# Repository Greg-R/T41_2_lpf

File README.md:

The documentation for this module is located here:

<https://kf5n.com/t41-2/t41-2_lpf/>

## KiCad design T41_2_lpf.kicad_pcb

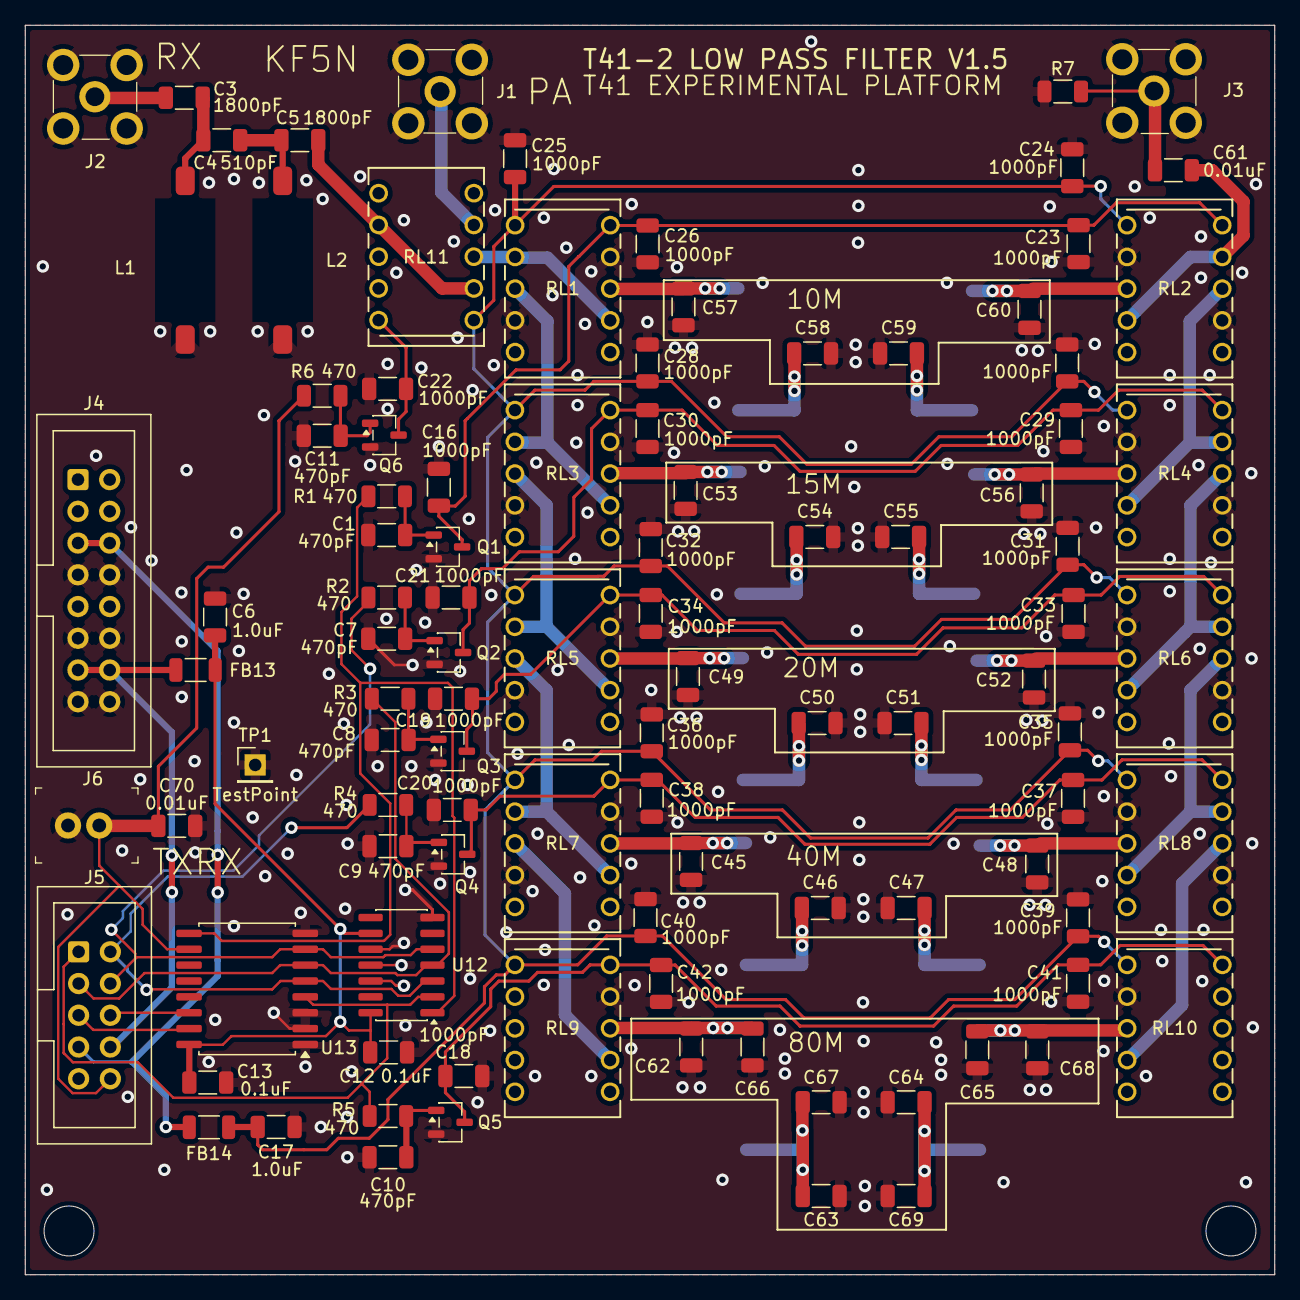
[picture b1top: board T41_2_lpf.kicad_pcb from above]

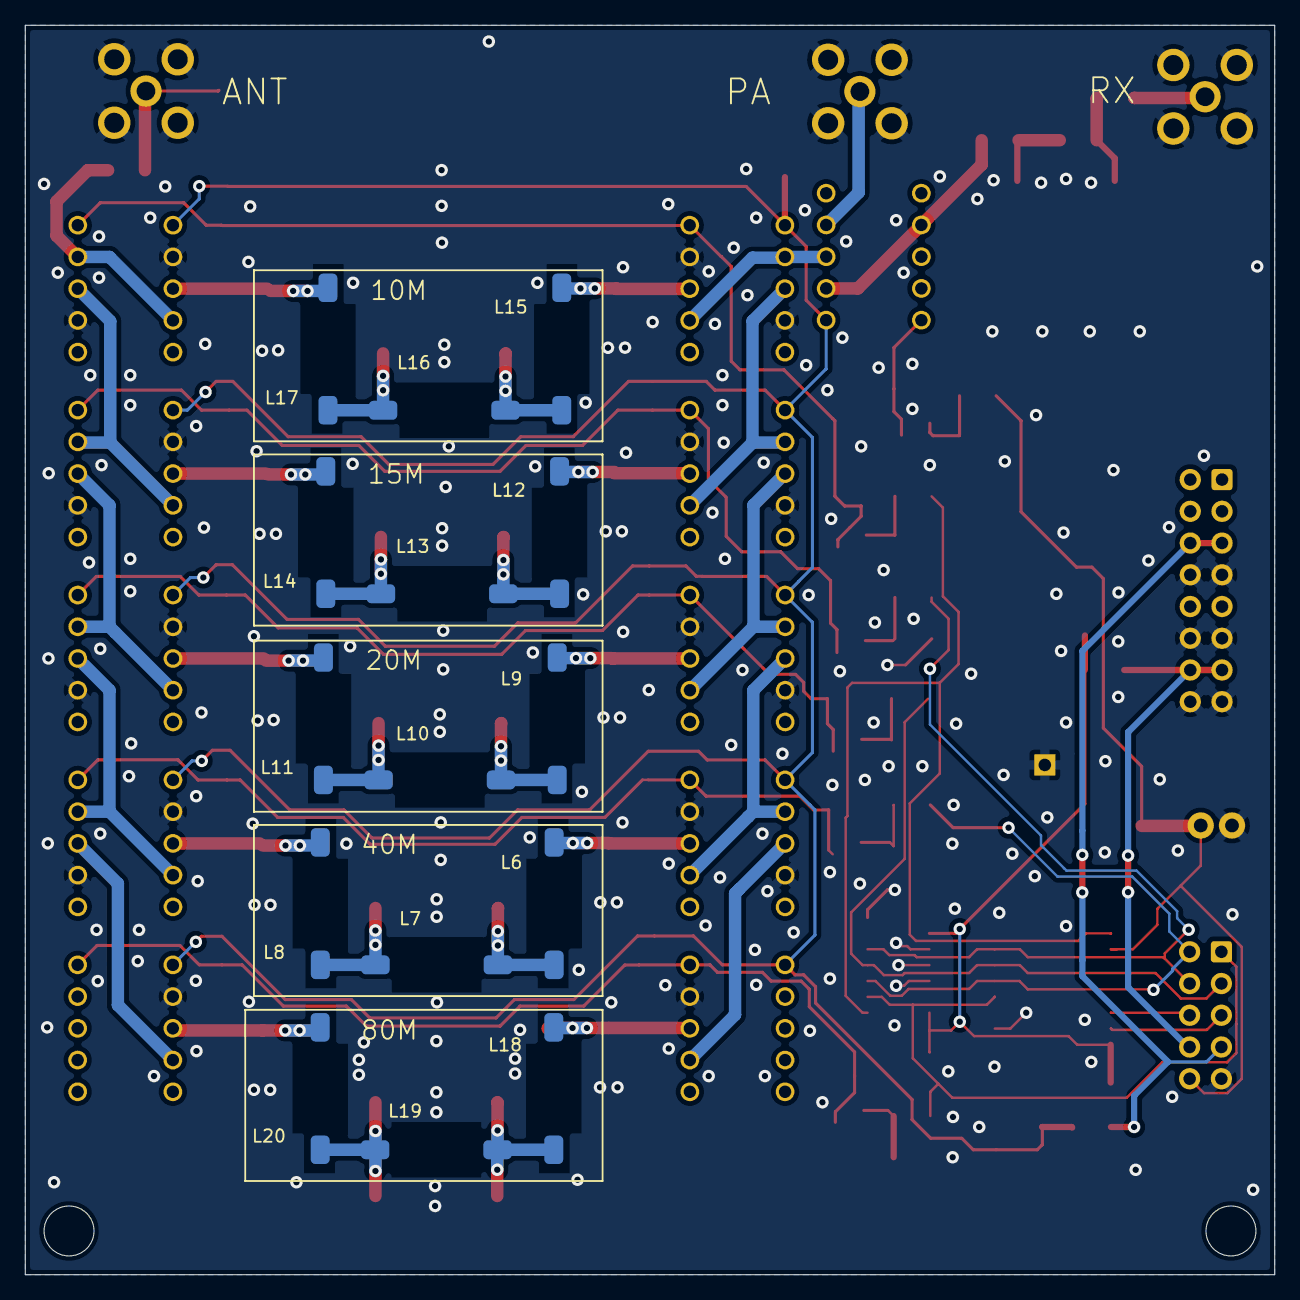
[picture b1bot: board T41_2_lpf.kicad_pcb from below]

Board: 2 copper layers, 100.0 x 100.0 mm, 117 parts (15 on the bottom side), 61 nets.

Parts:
C1, C7, C8, C9, C10, C11: 470pF; C_1206_3216Metric
C3, C5: 1800pF; C_1206_3216Metric
C4, C45, C48: 510pF; C_1206_3216Metric
C6, C17: 1.0uF; C_1206_3216Metric
C12, C13: 0.1uF; C_1206_3216Metric
C16, C18, C19, C20, C21, C22, C23, C24, C25, C26, C27, C28, C29, C30, C31, C32, C33, C34, C35, C36, C37, C38, C39, C40, C41, C42, C64, C65, C66, C67: 1000pF; C_1206_3216Metric
C46, C47: 1100pF; C_1206_3216Metric
C49, C52, C58, C59: 300pF; C_1206_3216Metric
C50, C51: 560pF; C_1206_3216Metric
C53, C56: 200pF; C_1206_3216Metric
C54, C55: 360pF; C_1206_3216Metric
C57, C60: 150pF; C_1206_3216Metric
C61, C70: 0.01uF; C_1206_3216Metric
C62, C68: 430pF; C_1206_3216Metric
C63, C69: 1500pF; C_1206_3216Metric
FB13, FB14: 28F0121-0SR-10; L_1206_3216Metric
J1, J2, J3: 5-1814832-1; RF_SMA_Vertical_5-1814832-1
J4: Conn_02x08_Odd_Even; IDC-Header_2x08_P2.54mm_Vertical
J5: Conn_02x05_Odd_Even; IDC-Header_2x05_P2.54mm_Vertical
J6: B2B-XH-A_LF__SN_; PinHeader_1x2_P2.5mm_Drill1.1mm
L1, L2: L; Toroid_SMD_T68
L6, L7, L8, L9, L10, L11, L12, L13, L14, L15, L16, L17, L18, L19, L20: L; Toroid_SMD_Thin
Q1, Q2, Q3, Q4, Q5, Q6: Q_NMOS_GSD; SOT-23-3
R1, R2, R3, R4, R5, R6: 470; R_1206_3216Metric
R7: 100k; R_1206_3216Metric
RL1, RL2, RL3, RL4, RL5, RL6, RL7, RL8, RL9, RL10, RL11: RELAY_TQ2_PAN
TP1: TestPoint; PinHeader_1x01_P2.54mm_Vertical
U12: 4002; SOIC-14_3.9x8.7mm_P1.27mm
U13: TCA9534; SOIC-16W_7.5x10.3mm_P1.27mm

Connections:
/3_3V_FIL: C6.1, C12.1, C13.1, FB13.2, U12.9, U12.14 (VDD), U13.16 (VDD)
/3_3V_IN: FB13.1, J4.13, J4.14, J5.8
/10M_ON: R1.1, U12.1, U13.9 (P4)
/12V_IN: FB14.1, J4.5, J4.6, J5.7
/12V_RELAY: C17.1, C24.2, C25.2, C27.2, C28.2, C31.2, C32.2, C35.2, C36.2, C39.2, C40.2, FB14.2, RL1.1, RL2.1, RL3.1, RL4.1, RL5.1, RL6.1, RL7.1, RL8.1, RL9.1, RL10.1, RL11.1
/15M_ON: J5.4, R2.1, U12.5, U13.7 (P3)
/20M_ON: J5.3, R3.1, U12.4, U13.6 (P2)
/40M_ON: J5.2, R4.1, U12.3, U13.5 (P1)
/80M_ON: J5.1, R5.1, U12.2, U13.4 (P0)
/Filter1/Input: C45.2, L6.1, RL7.8
/Filter1/Output: C48.2, L8.2, RL8.3
/Filter2/Input: C49.2, L9.1, RL5.8
/Filter2/Output: C52.2, L11.2, RL6.3
/Filter3/Input: C53.2, L12.1, RL3.8
/Filter3/Output: C56.2, L14.2, RL4.3
/Filter4/Input: C57.2, L15.1, RL1.8
/Filter4/Output: C60.2, L17.2, RL2.3
/Filter5/Input: C62.2, C66.2, L18.1, RL9.8
/Filter5/Output: C65.2, C68.2, L20.2, RL10.3
/SCL: J5.6, U13.14 (SCL)
/SDA: J5.5, U13.15 (SDA)
/TXRX: C70.1, J5.10, J6.2, R6.1, U13.10 (P5)
GND: C1.2, C6.2, C7.2, C8.2, C9.2, C10.2, C11.2, C12.2, C13.2, C16.2, C17.2, C18.2, C19.2, C20.2, C21.2, C22.2, C23.2, C24.1, C25.1, C26.2, C27.1, C28.1, C29.2, C30.2, C31.1, C32.1, C33.2, C34.2, C35.1, C36.1, C37.2, C38.2, C39.1, C40.1, C41.2, C42.2, C45.1, C46.1, C47.1, C48.1, C49.1, C50.1, C51.1, C52.1, C53.1, C54.1, C55.1, C56.1, C57.1, C58.1, C59.1, C60.1, C62.1, C63.1, C64.1, C65.1, C66.1, C67.1, C68.1, C69.1, C70.2, J1.1, J2.1, J3.1, J4.7, J4.8, J4.11, J4.12, J4.15, J4.16, J5.9, J6.1, L1.2, L2.2, Q1.2 (S), Q2.2 (S), Q3.2 (S), Q4.2 (S), Q5.2 (S), Q6.2 (S), R7.1, RL1.4, RL1.9, RL2.2, RL2.7, RL3.4, RL3.9, RL4.2, RL4.7, RL5.4, RL5.9, RL6.2, RL6.7, RL7.4, RL7.9, RL8.2, RL8.7, RL9.9, RL10.2, TP1.1 (1_1), U12.7 (VSS), U12.10, U12.11, U12.12, U13.1 (A0), U13.2 (A1), U13.3 (A2), U13.8 (GND)
unnamed: C3.1, C4.2, L1.1
unnamed: C3.2, J2.2
unnamed: C4.1, C5.2, L2.1
unnamed: C5.1, RL11.2, RL11.7
unnamed: C46.2, L6.2, L7.1
unnamed: C47.2, L7.2, L8.1
unnamed: C50.2, L9.2, L10.1
unnamed: C51.2, L10.2, L11.1
unnamed: C54.2, L12.2, L13.1
unnamed: C55.2, L13.2, L14.1
unnamed: C58.2, L15.2, L16.1
unnamed: C59.2, L16.2, L17.1
unnamed: C61.1, J3.2, R7.2
unnamed: C61.2, RL2.4, RL2.9
unnamed: C63.2, C67.2, L18.2, L19.1
unnamed: C64.2, C69.2, L19.2, L20.1
unnamed: J1.2, RL11.4
unnamed: C16.1, C23.1, C26.1, Q1.3 (D), RL1.10, RL2.10
unnamed: C1.1, Q1.1 (G), R1.2
unnamed: C21.1, C29.1, C30.1, Q2.3 (D), RL3.10, RL4.10
unnamed: C7.1, Q2.1 (G), R2.2
unnamed: C19.1, C33.1, C34.1, Q3.3 (D), RL5.10, RL6.10
unnamed: C8.1, Q3.1 (G), R3.2
unnamed: C20.1, C37.1, C38.1, Q4.3 (D), RL7.10, RL8.10
unnamed: C9.1, Q4.1 (G), R4.2
unnamed: C18.1, C41.1, C42.1, Q5.3 (D), RL9.10, RL10.10
unnamed: C10.1, Q5.1 (G), R5.2
unnamed: C22.1, Q6.3 (D), RL11.10
unnamed: C11.1, Q6.1 (G), R6.2
unnamed: RL1.2, RL1.7, RL11.3
unnamed: RL1.3, RL3.2, RL3.7
unnamed: RL2.8, RL4.4, RL4.9
unnamed: RL3.3, RL5.2, RL5.7
unnamed: RL4.8, RL6.4, RL6.9
unnamed: RL5.3, RL7.2, RL7.7
unnamed: RL6.8, RL8.4, RL8.9
unnamed: RL7.3, RL9.7
unnamed: RL8.8, RL10.4

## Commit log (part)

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2024-12-01 Initial commit.
2024-12-02 Ready for fab.
2025-12-28 Commit just prior to pushing to Github. Design not complete.
2026-03-15 Trying to improve schematic by adding capacitor values to all bands.
2026-03-21 T41-2 LPF V1.4 to fab.
2026-04-08 Work in progress just prior to publish.
2026-04-15 Ready to fab version 1.5
2026-04-15 Updated versions on schematic and layout to V1.5.
2026-04-19 Ready to release V1.5 to fab.
2026-04-22 Schematic clean-up.
2026-04-22 Repository clean-up.
2026-04-22 Cleaning up directories.
2026-04-23 Added revised README.md.
2026-04-23 Clean up directories.
2026-04-23 Cleaning directories.
2026-04-23 More clean-up.
2026-04-23 Updated schematic PDF.
2026-04-24 Deleted extraneous schematic.
2026-04-28 Final clean-up.
2026-04-28 Finally ready to push.
2026-04-30 Had to make minor change to accomodate V10/V11 Main Board.
2026-04-30 Updated PDF schematic.
2026-04-30 Added cap placement guide.
2026-05-01 Added license.
